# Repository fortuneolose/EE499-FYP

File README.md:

# EE499 FYP — Buck/Boost DC-DC Converter for Robotics and Autonomous Systems

Design, simulate, build and test a buck/boost DC-DC converter intended for use in robotics and autonomous systems such as factory automation, surveillance platforms, delivery robots, drones and e-mobility applications.

## Overview

DC-DC converters supply the various voltage rails required by different sub-systems in robotic platforms. This project investigates the key design principles of a switched-mode buck/boost converter, with emphasis on:

- **Efficiency** — targeting >97 % through low-power MOSFET switching and high-Q energy-storage components (inductors and capacitors).
- **Power quality** — minimising output voltage ripple introduced by the switching action to protect downstream sub-systems.
- **PWM control** — using pulse-width modulation to regulate the output voltage and current under varying load conditions.

## Repository Structure

| Folder | Contents |
|--------|----------|
| `LTSpice Boost Converter/` | LTSpice simulation schematics and waveform data for the LTC1871-based boost converter |
| `KiCAD PCB Design/` | KiCad schematic, PCB layout and project files |
| `EE499 Deliverables/` | Submitted project deliverables |
| `EE499 Checklist and Report Iterations/` | Report drafts and progress checklists |
| `Figures/` | Diagrams and images used in documentation |
| `Feedback Documents from Dr. Bob Lawlor/` | Supervisor feedback |
| `FYP_Template/` | Report and document templates |
| `auto_sync.sh`, `start_sync.bat` | Foreground Git Bash auto-sync (interval-based) |
| `sync_fyp.ps1`, `sync_fyp.vbs` | Background PowerShell sync (scheduled, silent) |

## Tools

- **LTSpice** — circuit simulation and AC/transient analysis
- **KiCad** — schematic capture and PCB layout
- **MATLAB / Simulink** — system-level modelling

## Repository Sync

Two mechanisms keep local clones in sync with this remote. Both commit, pull, and push automatically; `sync_fyp.log` captures activity.

- **Foreground watcher** — `start_sync.bat` launches `auto_sync.sh` in a Git Bash window (default 60 s interval). Handles divergence by preserving local work on a `backup/<host>/<timestamp>` branch before resetting to remote.
- **Background watcher** — `sync_fyp.vbs` runs `sync_fyp.ps1` silently (scheduled task, 15 min interval).

### Setting up on a new machine

`start_sync.bat` hardcodes the Git Bash executable path. On first setup, edit line 4 to point at the local Git install — e.g. `C:\Program Files\Git\bin\bash.exe` for a system-wide install, or `C:\Users\<user>\AppData\Local\Programs\Git\bin\bash.exe` for a per-user install. Run `where git` to check which one is present.

## Supervisor

Dr. Bob Lawlor

## References

1. EPC — DC-DC Converters for Industrial Applications
2. M. H. Rashid (Ed.), *Power Electronics Handbook*, 3rd Edition
3. A. S. Sedra, K. C. Smith et al., *Microelectronic Circuits*, 8th International Edition, Oxford University Press, 2021
4. R. Shaffer, *Fundamentals of Power Electronics with MATLAB*, Firewall Media, 2013

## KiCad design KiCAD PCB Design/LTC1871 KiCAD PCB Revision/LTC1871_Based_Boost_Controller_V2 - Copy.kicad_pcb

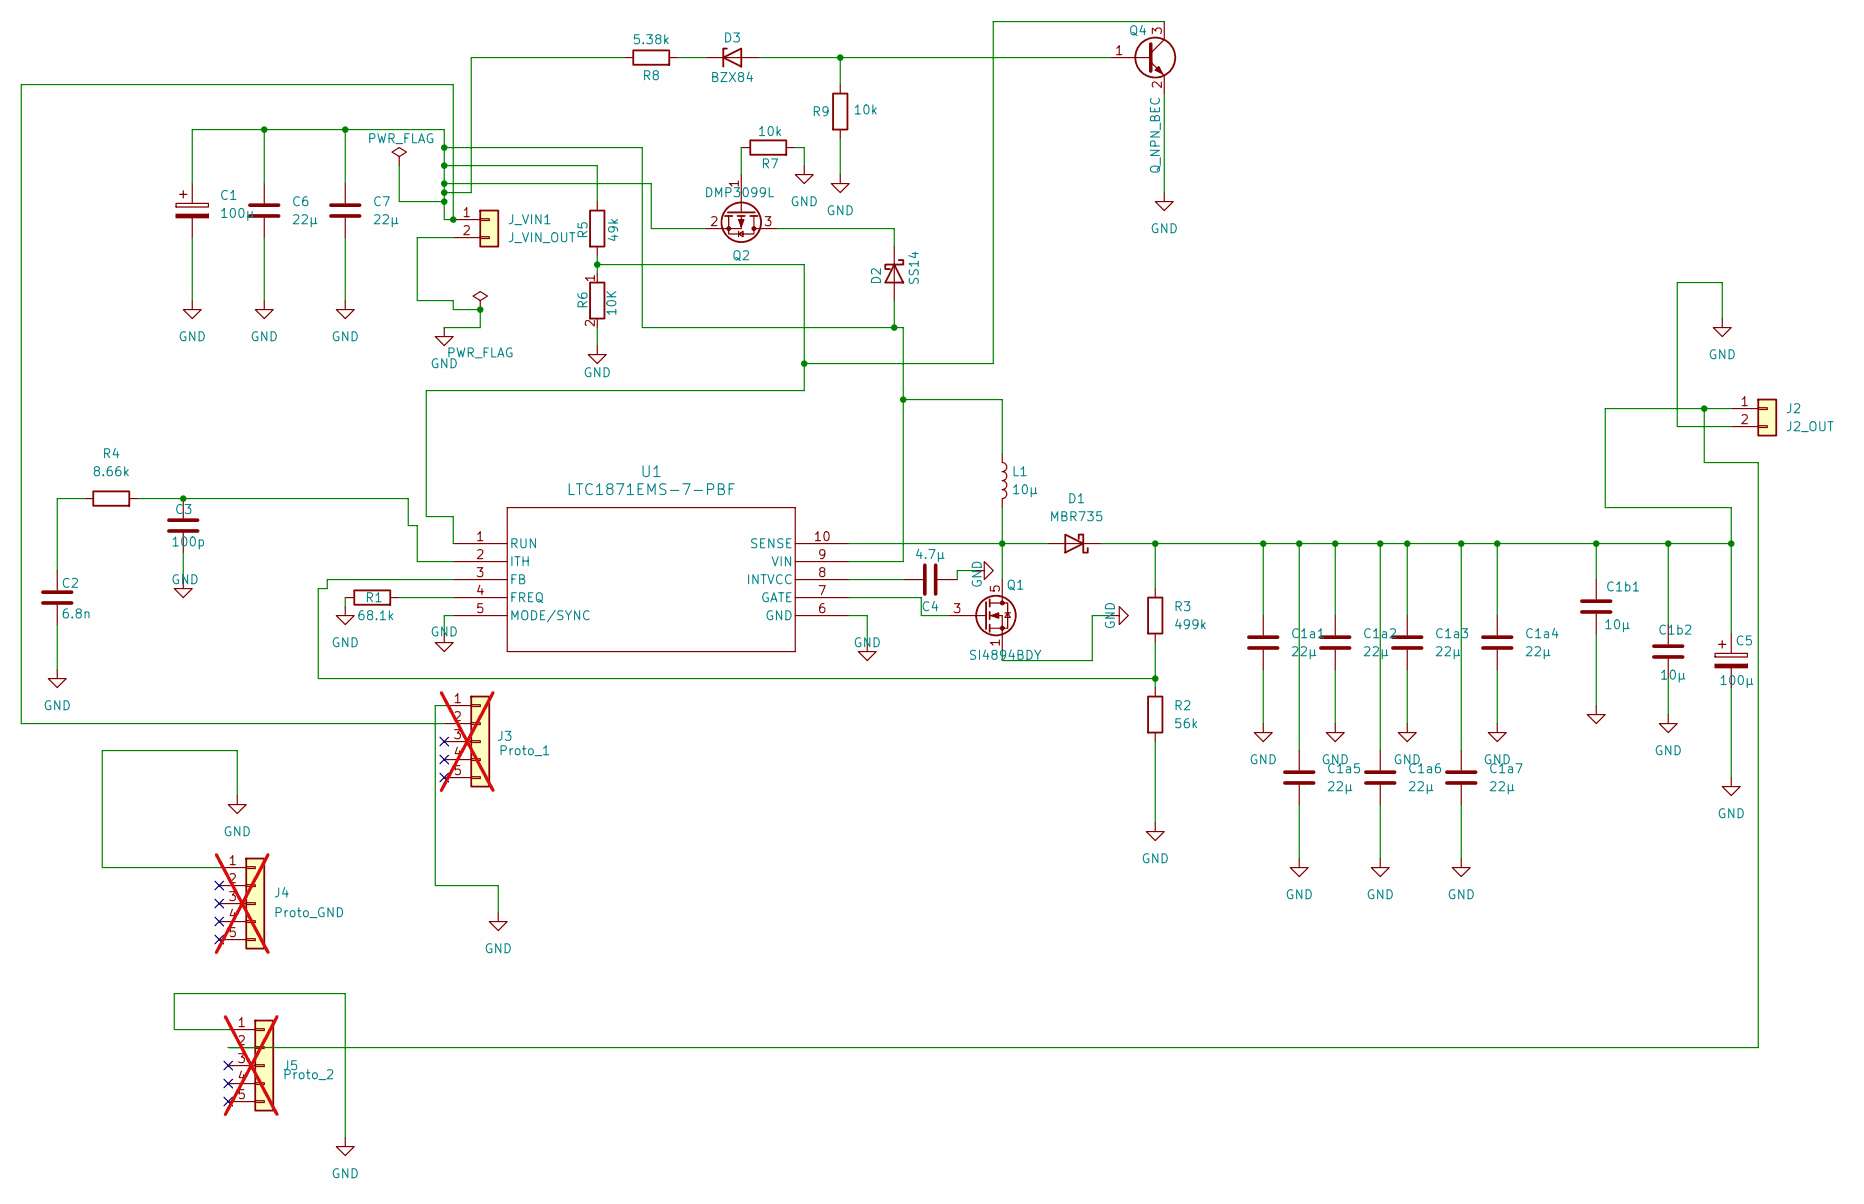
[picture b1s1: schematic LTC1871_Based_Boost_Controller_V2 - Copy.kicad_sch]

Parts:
C1, C5: 100µ; CP_Radial_D8.0mm_P3.50mm
C1a1, C1a2, C1a3, C1a4, C1a5, C1a6, C1a7, C6, C7: 22µ; C_1206_3216Metric
C1b1, C1b2: 10µ; C_0805_2012Metric
C2: 6.8n; C_0805_2012Metric
C3: 100p; C_0805_2012Metric
C4: 4.7µ; C_0805_2012Metric
D1: MBR735; TO-220-2_Vertical
D2: SS14; D_SMA
D3: BZX84; SOT-23
J2: J2_OUT; PinHeader_1x02_P2.54mm_Vertical
J3: Proto_1; PinHeader_1x05_P2.54mm_Vertical; not fitted
J4: Proto_GND; PinHeader_1x05_P2.54mm_Vertical; not fitted
J5: Proto_2; PinHeader_1x05_P2.54mm_Vertical; not fitted
J_VIN1: J_VIN_OUT; PinHeader_1x02_P2.54mm_Vertical
L1: 10µ; L_Coilcraft_XAL6060-XXX
Q1: SI4894BDY; SOIC-8_3.9x4.9mm_P1.27mm
Q2: DMP3099L; SOT-23
Q4: Q_NPN_BEC; SOT-23
R1: 68.1k; R_0805_2012Metric
R2: 56k; R_0805_2012Metric
R3: 499k; R_0805_2012Metric
R4: 8.66k; R_0805_2012Metric
R5: 49k; R_0805_2012Metric
R6: 10K; R_0805_2012Metric
R7: 10k; R_0805_2012Metric
R8: 5.38k; R_0402_1005Metric
R9: 10k; R_0402_1005Metric
U1: LTC1871EMS-7-PBF; MSOP-10_3x3mm_P0.5mm

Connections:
GND: C1.2, C1a1.2, C1a2.2, C1a3.2, C1a4.2, C1a5.2, C1a6.2, C1a7.2, C1b1.2, C1b2.2, C2.2, C3.2, C4.2, C5.2, C6.2, C7.2, J2.2, J3.1, J4.1 (Pin_1_1), J5.1, J_VIN1.2, Q1.1 (S), Q1.2 (Source), Q1.4 (Source), Q4.2 (E), R1.1, R2.2, R6.2, R7.2, R9.2, U1.5 (MODE/SYNC), U1.6 (GND)
unnamed: C2.1, R4.1
unnamed: D1.2 (A), L1.2, Q1.5 (D), Q1.6 (Drain), Q1.7 (Drain), Q1.8 (Drain), U1.10 (SENSE)
unnamed: C1a1.1, C1a2.1, C1a3.1, C1a4.1, C1a5.1, C1a6.1, C1a7.1, C1b1.1, C1b2.1, C5.1, D1.1 (K), J2.1, J5.2, R3.1
unnamed: C1.1, C6.1, C7.1, D2.2 (A), J3.2, J_VIN1.1, L1.1, Q2.2 (S), R5.1, R8.1, U1.9 (VIN)
unnamed: D2.1 (K), Q2.3 (D)
unnamed: D3.2 (A), Q4.1 (B), R9.1
unnamed: D3.1 (K), R8.2
unnamed: Q1.3 (G), U1.7 (GATE)
unnamed: Q2.1 (G), R7.1
unnamed: Q4.3 (C), R5.2, R6.1, U1.1 (RUN)
unnamed: R2.1, R3.2, U1.3 (FB)
unnamed: R1.2, U1.4 (FREQ)
unnamed: C4.1, U1.8 (INTVCC)
unnamed: C3.1, R4.2, U1.2 (ITH)

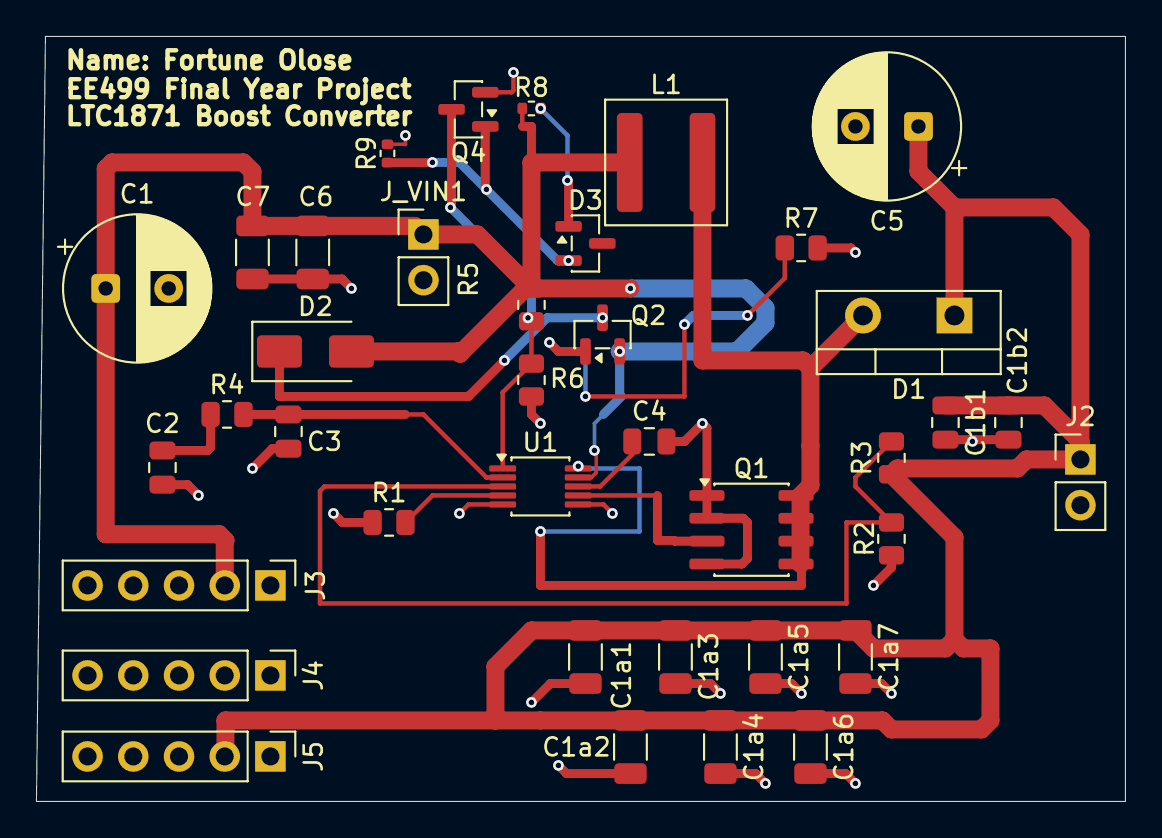
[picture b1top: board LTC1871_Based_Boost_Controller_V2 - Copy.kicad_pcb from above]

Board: 2 copper layers, 60.5 x 42.5 mm, 38 parts (0 on the bottom side), 15 nets.

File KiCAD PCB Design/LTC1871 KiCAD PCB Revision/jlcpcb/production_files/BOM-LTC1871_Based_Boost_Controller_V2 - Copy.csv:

Comment,Designator,Footprint,LCSC,Quantity
8.66k,R4,R_0805_2012Metric,,1
100p,C3,C_0805_2012Metric,,1
J_VIN_OUT,J_VIN1,PinHeader_1x02_P2.54mm_Vertical,,1
10µ,C1b2,C_0805_2012Metric,,1
J2_OUT,J2,PinHeader_1x02_P2.54mm_Vertical,,1
56k,R2,R_0805_2012Metric,,1
22µ,C1a4,C_1206_3216Metric,,1
49k,R5,R_0805_2012Metric,,1
22µ,C1a7,C_1206_3216Metric,,1
100µ,C5,CP_Radial_D8.0mm_P3.50mm,,1
22µ,C1a3,C_1206_3216Metric,,1
4.7µ,C4,C_0805_2012Metric,,1
6.8n,C2,C_0805_2012Metric,,1
10k,R7,R_0805_2012Metric,,1
22µ,C1a1,C_1206_3216Metric,,1
10µ,C1b1,C_0805_2012Metric,,1
499k,R3,R_0805_2012Metric,,1
22µ,C7,C_1206_3216Metric,,1
22µ,C1a6,C_1206_3216Metric,,1
68.1k,R1,R_0805_2012Metric,,1
SI4894BDY,Q1,SOIC-8_3.9x4.9mm_P1.27mm,,1
LTC1871EMS-7-PBF,U1,MSOP-10_3x3mm_P0.5mm,,1
10µ,L1,L_Coilcraft_XAL6060-XXX,,1
22µ,C1a5,C_1206_3216Metric,,1
SS14,D2,D_SMA,,1
100µ,C1,CP_Radial_D8.0mm_P3.50mm,,1
10K,R6,R_0805_2012Metric,,1
MBR735,D1,TO-220-2_Vertical,,1
22µ,C6,C_1206_3216Metric,,1
22µ,C1a2,C_1206_3216Metric,,1
DMP3099L,Q2,SOT-23,,1
10k,R9,R_0402_1005Metric,,1
5.38k,R8,R_0402_1005Metric,,1
Q_NPN_BEC,Q4,SOT-23,,1
BZX84,D3,SOT-23,,1

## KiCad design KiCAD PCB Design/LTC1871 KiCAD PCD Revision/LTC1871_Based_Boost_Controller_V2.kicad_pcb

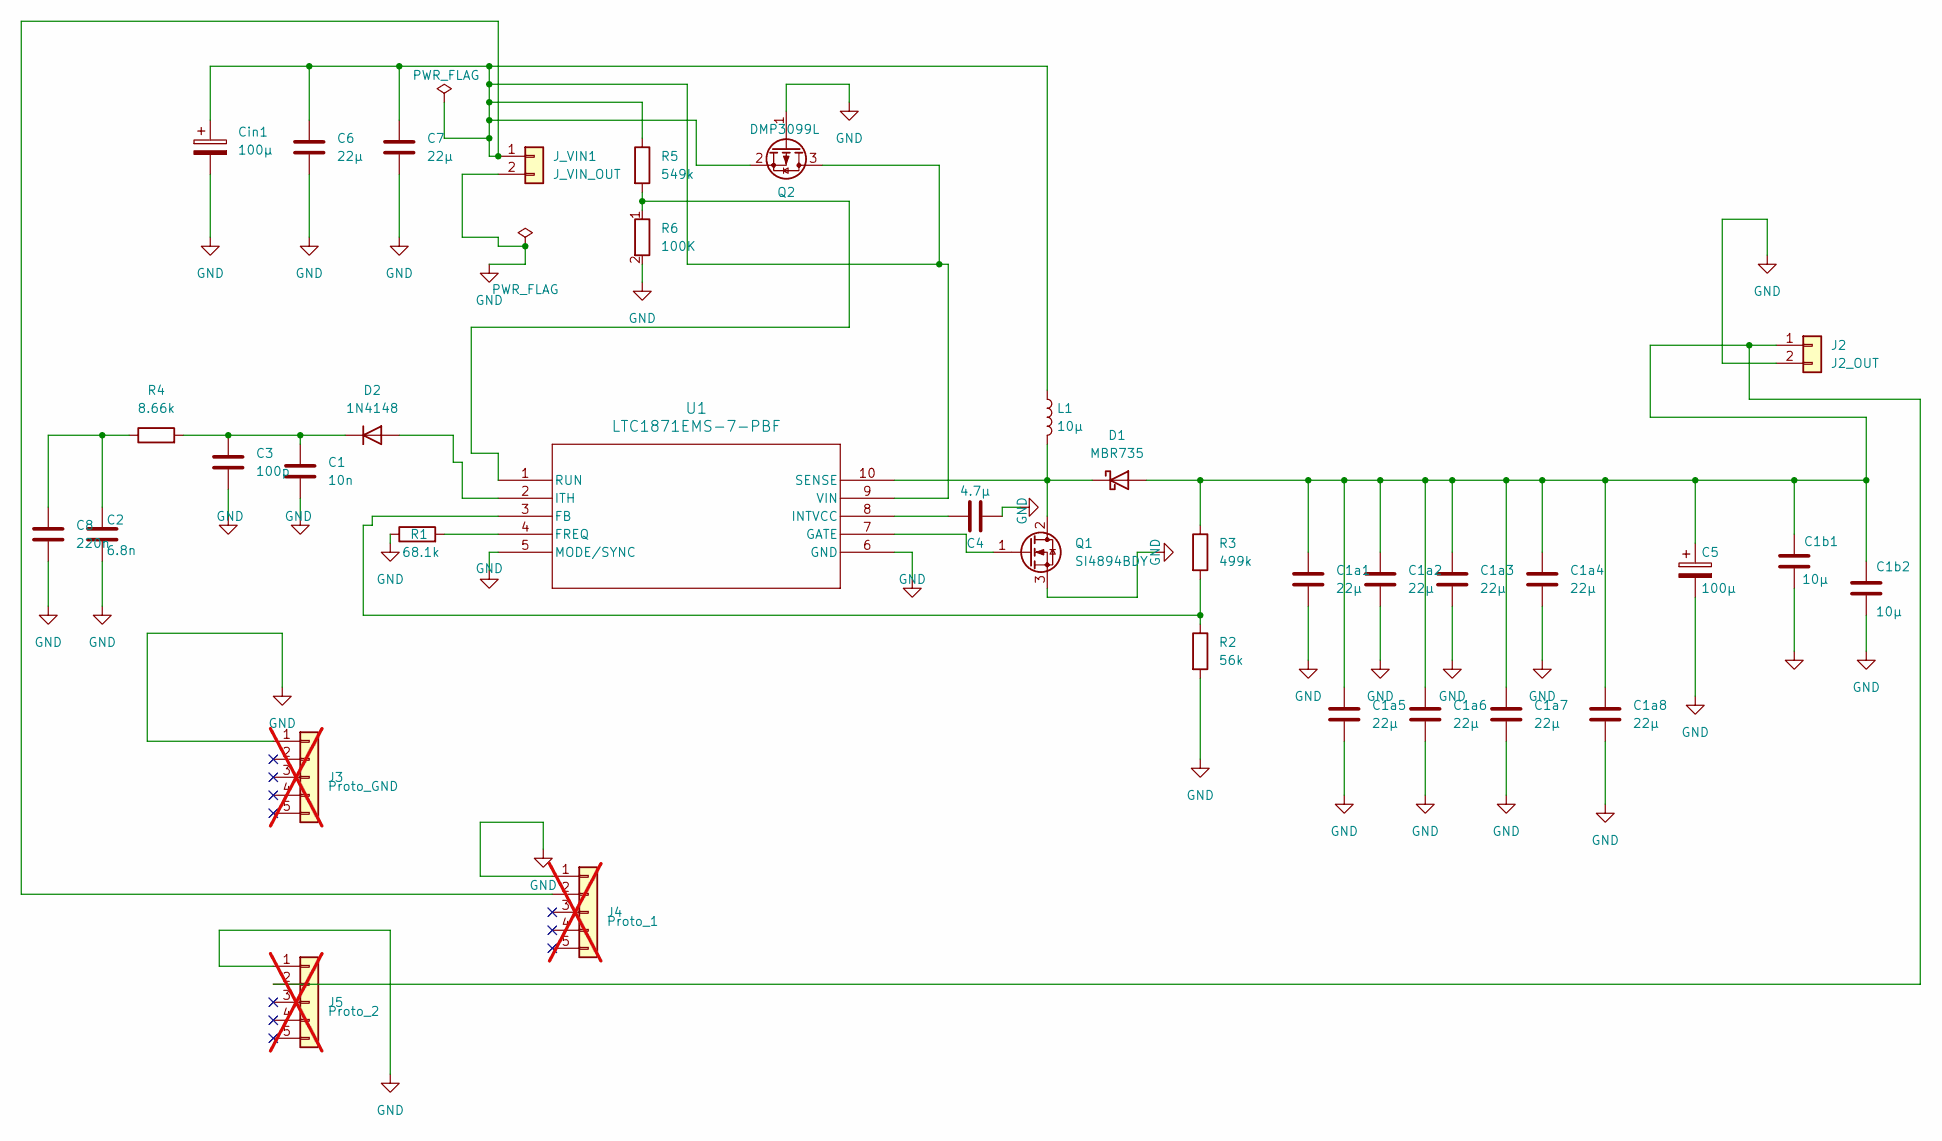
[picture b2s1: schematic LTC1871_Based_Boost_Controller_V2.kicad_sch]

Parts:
C1: 10n; C_0805_2012Metric
C1a1, C1a2, C1a3, C1a4, C1a5, C1a6, C1a7, C1a8, C6, C7: 22µ; C_1206_3216Metric
C1b1, C1b2: 10µ; C_0805_2012Metric
C2: 6.8n; C_0805_2012Metric
C3: 100p; C_0805_2012Metric
C4: 4.7µ; C_0805_2012Metric
C5: 100µ; CP_Radial_D8.0mm_P3.50mm
C8: 220n; C_0805_2012Metric
Cin1: 100µ; CP_Radial_D8.0mm_P3.50mm
D1: MBR735; D_DO-201AD_P15.24mm_Horizontal
D2: 1N4148; D_SOD-323_HandSoldering
J2: J2_OUT; PinHeader_1x02_P2.54mm_Vertical
J3: Proto_GND; PinHeader_1x05_P2.54mm_Vertical; not fitted
J4: Proto_1; PinHeader_1x05_P2.54mm_Vertical; not fitted
J5: Proto_2; PinHeader_1x05_P2.54mm_Vertical; not fitted
J_VIN1: J_VIN_OUT; PinHeader_1x02_P2.54mm_Vertical
L1: 10µ; L_Coilcraft_XAL6060-XXX
Q1: SI4894BDY; SOIC-8_3.9x4.9mm_P1.27mm
Q2: DMP3099L; SOT-23
R1: 68.1k; R_0805_2012Metric
R2: 56k; R_0805_2012Metric
R3: 499k; R_0805_2012Metric
R4: 8.66k; R_0805_2012Metric
R5: 549k; R_0805_2012Metric
R6: 100K; R_0805_2012Metric
U1: LTC1871EMS-7-PBF; MSOP-10_3x3mm_P0.5mm

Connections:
GND: C1.2, C1a1.2, C1a2.2, C1a3.2, C1a4.2, C1a5.2, C1a6.2, C1a7.2, C1a8.2, C1b1.2, C1b2.2, C2.2, C3.2, C4.2, C5.2, C6.2, C7.2, C8.2, Cin1.2, J2.2, J3.1 (Pin_1_1), J4.1, J5.1, J_VIN1.2, Q1.3 (S), Q2.1 (G), R1.1, R2.2, R6.2, U1.5 (MODE/SYNC), U1.6 (GND)
unnamed: C2.1, C8.1, R4.1
unnamed: C1a1.1, C1a2.1, C1a3.1, C1a4.1, C1a5.1, C1a6.1, C1a7.1, C1a8.1, C1b1.1, C1b2.1, C5.1, D1.2 (A), J2.1, J5.2, R3.1
unnamed: D1.1 (K), L1.2, Q1.2 (D), Q1.4 (Drain), Q1.5 (Drain), Q1.6 (Drain), Q1.7 (Drain), Q1.8 (Drain), U1.10 (SENSE)
unnamed: D2.2 (A), U1.2 (ITH)
unnamed: C1.1, C3.1, D2.1 (K), R4.2
unnamed: C6.1, C7.1, Cin1.1, J4.2, J_VIN1.1, L1.1, Q2.2 (S), Q2.3 (D), R5.1, U1.9 (VIN)
unnamed: Q1.1 (G), U1.7 (GATE)
unnamed: R2.1, R3.2, U1.3 (FB)
unnamed: R1.2, U1.4 (FREQ)
unnamed: C4.1, U1.8 (INTVCC)
unnamed: R5.2, R6.1, U1.1 (RUN)

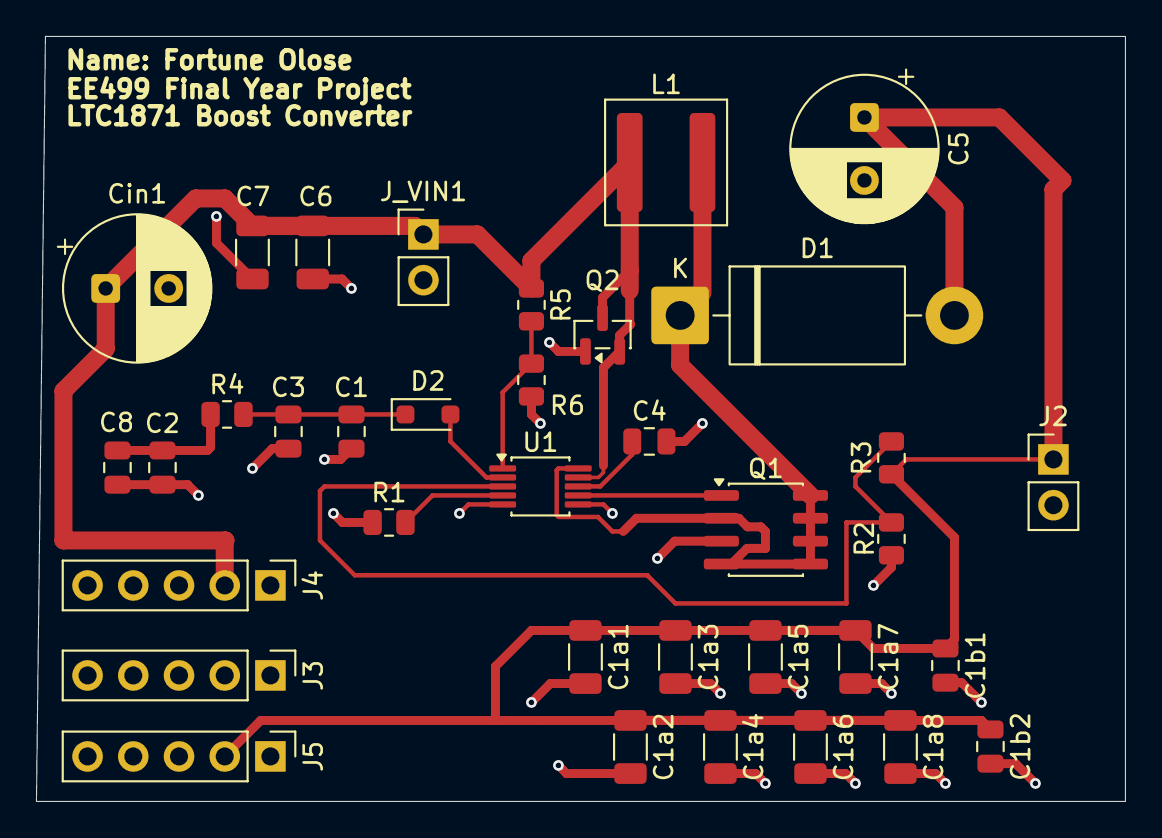
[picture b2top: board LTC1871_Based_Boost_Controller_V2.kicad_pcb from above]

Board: 2 copper layers, 60.5 x 42.5 mm, 36 parts (0 on the bottom side), 12 nets.

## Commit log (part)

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2026-04-06 Auto-sync from Fortune at 2026-04-06 14:13:53
2026-04-06 Auto-sync from Fortune at 2026-04-07 00:22:32
2026-04-07 Auto-sync from Fortune at 2026-04-07 09:49:01
2026-04-07 Auto-sync from Fortune at 2026-04-07 10:08:35
2026-04-08 Auto-sync from Fortune at 2026-04-08 13:10:18
2026-04-08 Auto-sync from Fortune at 2026-04-08 13:28:10
2026-04-08 Auto-sync from Fortune at 2026-04-08 16:47:45
2026-04-08 Auto-sync from Fortune at 2026-04-08 18:12:47
2026-04-08 Auto-sync from Fortune at 2026-04-08 18:14:10
2026-04-08 Auto-sync from Fortune at 2026-04-08 18:28:44
2026-04-08 Auto-sync from Fortune at 2026-04-08 18:43:08
2026-04-08 Auto-sync from Fortune at 2026-04-08 18:58:33
2026-04-08 Auto-sync from Fortune at 2026-04-08 19:17:59
2026-04-08 Auto-sync from Fortune at 2026-04-08 19:27:48
2026-04-08 Auto-sync from Fortune at 2026-04-08 19:29:11
2026-04-08 Auto-sync from Fortune at 2026-04-08 19:32:21
2026-04-08 Auto-sync from Fortune at 2026-04-08 19:34:28
2026-04-08 Auto-sync from Fortune at 2026-04-08 19:54:42
2026-04-08 Auto-sync from Fortune at 2026-04-08 19:59:30
2026-04-08 Auto-sync from Fortune at 2026-04-08 20:14:14
2026-04-08 Auto-sync from Fortune at 2026-04-08 20:29:12
2026-04-08 Auto-sync from Fortune at 2026-04-08 20:43:48
2026-04-08 Auto-sync from Fortune at 2026-04-08 20:59:15
2026-04-08 Auto-sync from Fortune at 2026-04-08 21:36:22
2026-04-08 Auto-sync from Fortune at 2026-04-08 21:37:35
2026-04-08 Auto-sync from Fortune at 2026-04-08 21:38:57
2026-04-08 Auto-sync from Fortune at 2026-04-08 23:37:36
2026-04-08 Auto-sync from Fortune at 2026-04-08 23:49:32
2026-04-09 Auto-sync from Fortune at 2026-04-09 08:51:17
2026-04-09 Auto-sync from Fortune at 2026-04-09 18:59:21
2026-04-09 Auto-sync from Fortune at 2026-04-09 20:51:06
2026-04-09 Auto-sync from Fortune at 2026-04-10 00:15:56
2026-04-10 Auto-sync from Fortune at 2026-04-10 15:43:13
2026-04-10 Auto-sync from Fortune at 2026-04-10 17:12:48
2026-04-10 Auto-sync from Fortune at 2026-04-10 17:14:57
2026-04-10 Auto-sync from Fortune at 2026-04-10 17:22:10
2026-04-10 Auto-sync from Fortune at 2026-04-10 17:23:14
2026-04-10 Auto-sync from Fortune at 2026-04-10 17:58:44
2026-04-10 Auto-sync from Fortune at 2026-04-10 18:03:58
2026-04-10 Auto-sync from Fortune at 2026-04-10 21:47:52
2026-04-11 Auto-sync from Fortune at 2026-04-11 22:57:18
2026-04-13 Auto-sync from Fortune at 2026-04-13 06:50:55
2026-04-13 Auto-sync from Fortune at 2026-04-13 06:54:09
2026-04-13 Auto-sync from Fortune at 2026-04-13 21:30:20
2026-04-13 Auto-sync from Fortune at 2026-04-13 22:49:59
2026-04-13 Auto-sync from Fortune at 2026-04-13 23:02:02
2026-04-13 Auto-sync from Fortune at 2026-04-13 23:12:01
2026-04-13 Auto-sync from Fortune at 2026-04-13 23:20:11
2026-04-14 Auto-sync from Fortune at 2026-04-14 15:01:52
2026-04-14 Auto-sync from Fortune at 2026-04-14 15:35:52
2026-04-15 Auto-sync from Fortune at 2026-04-15 19:20:39
2026-04-18 Auto-sync from Fortune at 2026-04-18 21:09:09
2026-04-18 Auto-sync from Fortune at 2026-04-18 21:15:59
2026-04-19 Auto-sync from Fortune at 2026-04-19 09:47:09
2026-04-20 Auto-sync from Fortune at 2026-04-20 05:29:32
2026-04-20 Auto-sync from Fortune at 2026-04-20 06:51:06
2026-04-22 Auto-sync from EECR-HN3V674 at 2026-04-22 16:37:02
2026-04-22 Auto-sync from EECR-HN3V674 at 2026-04-22 19:15:46
2026-04-22 Auto-sync from EECR-HN3V674 at 2026-04-22 19:15:57
2026-04-22 Auto-sync from EECR-HN3V674 at 2026-04-22 19:29:39
2026-04-22 Auto-sync from Fortune at 2026-04-23 00:30:17
2026-04-23 Auto-sync from Fortune at 2026-04-23 06:58:40
2026-04-23 Auto-sync from Fortune at 2026-04-23 08:24:03
2026-04-23 Auto-sync from EECR-HN3V674 at 2026-04-23 21:03:28
2026-04-24 Auto-sync from Fortune at 2026-04-24 10:23:43
2026-04-24 Auto-sync from Fortune at 2026-04-24 18:05:31
2026-04-24 Auto-sync from Fortune at 2026-04-24 18:16:23
2026-04-26 Auto-sync from Fortune at 2026-04-26 07:34:23
2026-04-26 Auto-sync from Fortune at 2026-04-26 22:20:36
2026-04-26 Auto-sync from Fortune at 2026-04-27 00:52:10
2026-04-27 Auto-sync from EECR-HN3V674 at 2026-04-27 17:53:45
2026-04-28 Auto-sync from Fortune at 2026-04-28 21:40:39
2026-04-28 Auto-sync from Fortune at 2026-04-29 00:41:52
2026-04-30 Auto-sync from EECR-HN3V674 at 2026-04-30 18:59:04
2026-04-30 Auto-sync from EECR-HN3V674 at 2026-04-30 19:48:01
2026-04-30 Auto-sync from EECR-HN3V674 at 2026-04-30 21:56:22
2026-05-01 Auto-sync from EECR-HN3V674 at 2026-05-01 19:06:08
2026-05-01 Auto-sync from EECR-HN3V674 at 2026-05-01 21:54:41
2026-05-01 Auto-sync from EECR-HN3V674 at 2026-05-01 22:00:23
2026-05-04 Auto-sync from Fortune at 2026-05-04 16:17:24
2026-05-05 Auto-sync from Fortune at 2026-05-05 08:49:35
2026-05-05 Auto-sync from Fortune at 2026-05-05 12:00:42
2026-05-05 Auto-sync from Fortune at 2026-05-05 17:58:13
2026-05-05 Auto-sync from Fortune at 2026-05-05 18:20:32
2026-05-05 Auto-sync from Fortune at 2026-05-05 18:41:26
2026-05-05 Auto-sync from Fortune at 2026-05-05 20:41:52
2026-05-05 Auto-sync from Fortune at 2026-05-05 20:55:24
2026-05-06 Auto-sync from Fortune at 2026-05-06 01:04:25
2026-05-07 Auto-sync from Fortune at 2026-05-07 01:50:28
2026-05-08 Auto-sync from Fortune at 2026-05-08 08:40:33
2026-05-08 Auto-sync from Fortune at 2026-05-08 22:26:05
2026-05-13 Auto-sync from Fortune at 2026-05-13 17:30:12
2026-05-13 Auto-sync from Fortune at 2026-05-13 17:36:52
2026-05-13 Auto-sync from Fortune at 2026-05-13 17:38:05
2026-05-13 Auto-sync from Fortune at 2026-05-13 17:38:31
2026-05-13 Auto-sync from Fortune at 2026-05-13 17:39:44
2026-05-13 Auto-sync from Fortune at 2026-05-13 17:42:57
2026-05-13 Auto-sync from Fortune at 2026-05-13 18:46:56
2026-05-14 Auto-sync from EECR-HN3V674 at 2026-05-14 17:58:46
